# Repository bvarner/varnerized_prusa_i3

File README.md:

# Varnerized Prusa i3 3D Printer Clone

This is a project to produce a 3d printer based upon the (very excellent) work of Mr. Josef Prusa, and the 3d printing community at large.

After playing with an i3 MK2.5 my office at the time acquired I found some guides online for building your own printer inspired by the Prusa design.
Specifically, [Tom's Dolly Build](https://toms3d.org/2017/02/23/building-cheapest-possible-prusa-i3-mk2/) was highly inspiring.

I'm willing to sacrifice _some_ asthetics, a bit of performance, the 'ease' of pre-integration, and get an education for the sake of cost cutting.
As in the early heady days of the PC industry... building a 'clone' from imported components is cheaper than purchasing the fully assembled and configured machine.

## Goal of the project.

To clone a Prusa i3 with very similar mechanics, using import parts and cheaper, more-modular electronics.
My initial budget for the build is $225. With that budget, I produced a wooden framed i3 clone, using an Arduino & RAMPS board with A4988 stepper drivers, knockoff E3D V6 hotend, and an aluminum heated bed.

I have since upgraded some things considerably, in a price-conscious manner, and well behind the bleeding edge, so that I can source parts inexpensively.

This isn't just an attempt to build a clone and leave it alone. In keeping with the RepRap / Prusa mentality, my desire is to build a device that allows for replicating / designing / implementing more advanced subsequent generations.

## This Repository / Branch Strategy

The 'master' branch here will reflect the current (stable, functioning) state of the project - the machine I'm currently running, or the last state of the machine.
The 'development' branch will track be the next iteration of updates / upgrades.

# 1.3 - Volcano Hotend & Belt Tensioning
Over the years I've had problems with bearings coming loose from the x-axis ends. I held them in place with zip-ties for more than a year.
My pancake stepper with the skelestruder gave me phenomical prints, but I had many problems with stability of the hotend holding temp during high extrusion rates or aggressive part cooling fan use.

In order to print things faster (I'm sick of waiting four hours for a tiny part) and with thicker layers, I have upgraded to a Volcano knock-off hotend -- which the skelestruder supports beautifully.
I've also decided to print my entire hotend assembly in polycarbonate, as I was having multiple parts sag over time and when printing high-temp filaments (like PC or nylon).

I ended up having to upgrade to a slightly larger pancake motor, as I exceeded the torque of the tiny pancake before I exceeded the reasonable flow rate of a 0.6mm CHT volcano nozzle.

A 200g spool of PC is more than enough to print the entire extruder and omega several times over.

Credits to the folks who made these fantastic parts that I'm using:
[X-Axis](https://www.printables.com/model/394668-mk225s-x-axis-revision-with-belt-tensioner)
[Y-Axis Tensioner](https://www.printables.com/model/306303-y-axis-belt-tensioner-v2)

# 1.2 - Skelestruder.
Having some shore 95A flex filament to print, the MK3 extruder design is rubbish. I've had issues with part cooling, part visibility during print, z-axis adjustment, it's been a problem. Futhermore I get a lot of obvious print quality issues with linear advance and the direct drive extruder with 1/16th step division.
The [Skelestruder](https://www.thingiverse.com/thing:2845416) is designed to address all of that, and after having it for a few weeks, it was obvious it's a superior design.

Additionally, a friend of mine supplied me with a Prusa Mini+ filament sensor kit, which I've integrated into my build using 
this [skelestruder sensor cover](https://www.thingiverse.com/thing:4235461).

Initially I printed everything in PETG, without a silicone sock and insulation at the top of the heat block. This caused EcageS to melt a couple times, and deformed some other parts when I attempted to print Nylon at high-temperatures.
To combat this problem, I've reprinted some parts in Polycarbonate. I purchased a 200g trial spool for a reasonable fee.

* Printed Parts
    * Polycarbonate
        * SP_EcageS_r1.stl
        * SP_Omega_r2.stl
        * SP_Pinion16_r1.stl
        * SP_Pinion14_r1.stl
        * [SP_Xclamp_mk2.stl](https://www.thingiverse.com/thing:3699231)
    * PETG
        * SP_Carriage_r1.stl
        * SP_tail_b2.stl
        * SP_EcageB_r1.stl
        * SP_EcageF17_r1.stl
        * SP_Shroud_r1.stl
        * SP_Key_r1.stl
        * Inlet_ptfe_r1b.stl
        * SP_Spider17_r1.stl
        * SP_Wheel_r1.stl
        * SP_Tread56_r1.stl
        * SP_Prack_r1.stl
        * SP_Idler_r1.stl
        * SP_tensioner_b1.stl
        * SP_knob_b2.stl
        * SP_spacer_v1a4.stl
        * IR_Sensorcover_top.stl
        * IR_Sensorcover_outlet.stl
        * IR_Sensorcover_bottom.stl
        * IR_Sensor_Arm.stl
* Purchased Parts
    * [GT2 140-2GT-6](https://www.amazon.com/gp/product/B014QJBVOY/ref=ppx_yo_dt_b_asin_title_o00_s00?ie=UTF8&psc=1)
    * [Polyimide (Kapton) tape](https://www.amazon.com/gp/product/B00W3FAFP0/ref=ppx_yo_dt_b_asin_title_o04_s00?ie=UTF8&psc=1)
    * [105zz bearings](https://www.amazon.com/gp/product/B00ZHSTKCE/ref=ppx_yo_dt_b_asin_title_o07_s00?ie=UTF8&psc=1)
    * [5mmx100mm shafts](https://www.amazon.com/gp/product/B01B27MJC6/ref=ppx_yo_dt_b_asin_title_o07_s01?ie=UTF8&psc=1) I cut and shaped these with an angle grinder.
    * [12v 5015 fans](https://www.amazon.com/gp/product/B07LF1V1P1/ref=ppx_yo_dt_b_asin_title_o07_s01?ie=UTF8&psc=1) My original cooling fan died.
    * [Prusa IR filament sensor](https://www.aliexpress.com/item/32976810546.html?spm=a2g0o.productlist.0.0.115d21ee6SdBZw&algo_pvid=dfe3353a-f8a1-4ab3-83c8-9e795aa067fe&algo_exp_id=dfe3353a-f8a1-4ab3-83c8-9e795aa067fe-0)
    * [Heatblock Top Insulation](https://www.amazon.com/gp/product/B075CST527/ref=ppx_yo_dt_b_asin_title_o08_s00?ie=UTF8&psc=1) I used this between the heatbreak and the heatblock.
    * [Heatblock Silicone Sock](https://www.amazon.com/gp/product/B07Q3KHL6R/ref=ppx_yo_dt_b_asin_title_o09_s00?ie=UTF8&psc=1) How did I go so many years without a silicone sock?

# 1.1.1 - Lack Table Enclosure.
Following the [prusaprinters blog post](https://blog.prusaprinters.org/cheap-simple-3d-printer-enclosure/) on building an inexpensive (hah!) enclosure for your printer I recently picked up a couple of Ikea LACK tables.
After getting local quotes for producing the 440x440 and 440x220 acrylic panels, I opted to buy a set from a vendor on Amazon who could beat the locally sourced prices.

* Printed Parts
    * PSU Shroud
        * Compatible with the Prusa Lack table mounting clip (mounting foot geometry is closer to the Prusa part)
        * Added Lack Table PSU retainer. Similar Style as the Prusa version.
        * Text rotates to the upside down orientation on the PSU Shroud if you're rendering the LACK table parts.
    * [Ikea LACK Enclosure Main Parts](https://www.thingiverse.com/thing:2864118)
    * [Frame brace replacing the PSU for the MK3](https://www.thingiverse.com/thing:2859884)
    * [60 degree heatbed cable cover for the MK3](https://www.thingiverse.com/thing:2890592)
    * [608 bearing wheels for the adjustable spool holder](https://www.thingiverse.com/thing:3791583)
    * [Prusa Enclosure Bottom Corner with more cable space](https://www.thingiverse.com/thing:3067172)
    * [IKEA Lack Table Stack Coupler](http://www.thingiverse.com/thing:3488697)
* Purchased Parts
    * #12 AWG Silicone wire. So much better to work with than THHN.
    * XT60H Connectors
    * misc. dupont connectors & hookup wire (from the scrap bin)
    * (3) IRLB3034 N-Channel Mosfets & 10k Ohm 0805 SMT Resistors.
    * 12v RGB LED 5050 Strip (I had leftovers from another home project)
* @Home Fabricated PCB For Controlling RGB LEDs
    * Check the LEDControl directory for full KiCAD project.
    * Perfect for home-based acid etching and SMT hand soldering.
    * I use the 'laser-printer hot-iron transfer' method, and it works quite well.

# 1.1.0 - More MK3 less, MK2.
Total upgrade cost was ~$75 in January 2018.

* Heat-Bed
    * I replaced my aluminum MK3 heat bed with a magnetic MK52, 12V heat bed.
    * It's not as 'flat' as the prusa originals.
    * Cost was ~$36, as opposed to the original one which was ~$8.
    * Spring steel sheet + PEI cost around another $25. At this time, I'd opt for the powder-coated textured spring steel instead.
* Extruder
    * Uses the BondTech style extruder pulleys
    * Improved part cooling
    * 5v Noctua Fan reduces ambient noise considerably
    * I did not add a filament sensor (yet) or a dust-buffer (yet).
* Electronics
    * After having beefed up the ampacity of the RAMPS 1.4a board, and replacing the heatbed mosfet, I decided to try a RAMPS 1.6 board.
    * Much better experience than the RAMPS 1.4a.
    * After 11 months of use, no over-heating issues. No fried mosfets, no fire risk. Much better electronics from that stand point.
    * Heat bed does heat slowly, a consequence of the mosfet choice on this board, from what I understand.
    * I've updated my firmware to Marlin 1.1.9, and "Varnerized" it to match the Prusa Home Screen Asthetic on the LCD.
    * Updated RAMBo cover a bit. I ended up reprinting in PETG and got much better results than with the original PLA. It also hasn't sagged and melted in my hot-box.
* Mechanics
    * Y-Axis bearing holders have been redone, and are now my own design that allows for slight play.
    * I think I've fixed the issues with the y-axis belt holder not contacting the limit switch properly.
    * Updates to the TR8_couplings have resulted in much better Z-axis stability.
    * heatbed cable cover -- based on using ring terminals and heavy gauge speaker wire -- is _very_ large compared to the MK3.

# 1.0.0 - Hybrid MK2s & MK3
The original starting point. 1 Spool of ABS, a few scraps of cabinet grade plywood, access to a working MK2, and about $165 in imported parts.

* Heat-Bed - I chose a 3mm thick aluminum MK3 (Ultimaker clone) 200x200mm.
    * This gives me a slightly smaller build area than an Original Prusa.
    * No 'fully-automatic' skew compensation.
        * The aluminum bed of the MK3 will still work for automatic z-layer leveling.
        * Guided x-y skew measurement and compensation will be required.
    * I did pony up for a sheet of PEI plastic to cover the aluminum bed and improve adhesion. That was worth it.
* Steppers - I used an inexpensive 5-pack of 5mm output shaft steppers that put out ~40n-cm of torque.
    * My Z-Axis motors require couplings to the lead screws.
    * I did pony up for T8 ACME lead screws and nuts for the Z-axis. The small cost should be worth the improved ridgidity and accuracy.
* Electronics - Arduino Mega 2650 + RAMPS 1.4a
    * Won't be nearly as nicely packaged as a mini-rambo... until I print my own case design to make it not ugly.
    * Will have to custom-compile firmware from the Marlin project.
    * More flexibility in the long-run with regards to expansion and addition of other sensors.
    * I used a 30Amp, 12v power supply (360 Watt). I was able to get this for $20 from Amazon, which was only slightly more expensive than the best priced 240Watt imported supply. Low quantities of heavy items are expensive to ship.
    * I'm going to just bypass the poly-fuses on the RAMPS board and add properly sized inline fuses. Perhaps someday I'll replace the RAMPs board. Perhaps Not.
* Frame - I'm making mine out of wood.
    * Won't be as svelt as a Prusa from the side, and may warp / twist slightly with seasonal changes. I'll be using thing-laminations of quarter-sawn lumber or cabinet-grade plywood to minimize this.
    * Major reduction of cost here. An MK2 aluminum frame runs ~$70. Laser-cut acrylic and wood are cheaper, but less rigid, and won't be as nice as mine.
    * Basing off the MK3 frame (which uses 3030 extrusions rather than threaded rods) translates more easily to wood.
    * I have a pretty well equipped wood shop, with 40 year old tools that are accurate +- 0.254mm and within a half-degree of cross-cut. I have calipers. I'll be able to correct for skew. :-)

## Printed Parts Lineage / Changes

* Y-Axis (under heatbed carriage) -- Mostly from the MK3. The necessity of an endstop swtich necessitates some changes to the Y-Motor mount. I am expecting to need to modify the rear frame DXF to reflect modifications / changes. I may not have room for the limit switch microswitch. Also, the belt holder for y-frame may need modification.
* X-Axis (gantry above heatbed) -- Completely from the MK2s.
* Z-Axis -- Mostly from the MK3. The T8 leadscrew will likely extend beyond the upper limit of the MK3 frames upper z-ends. I modified the MK3 parts to 'open' the top of the leadscrew holes and the rod holding hole -- ala a MK2/s. I figure this will be easier than cutting a T8 rod.
* Extruder -- Completely from the MK2s. I may look into the cogged dual-feed of the MK3 at some point, but until the Prusa fillament sensor board clones start to appear, there's really no reason to do that.
    * I will need to wait until my induction probe arrives to make sure it's the same physical size as the PINDA and avoid re-printing.
    * Thankfully for the Z-axis I don't need an end-stop limit switch.
* LCD -- Assuming my LCD fits the frame properly, I'll use the Prusa design...

### Print Settings

Prusa uses ABS, 20% infill, 3 perimeter (vertical) shells on a 0.4mm nozzle. The rest, well that's up to you. :-)
The three vertical shells are incredibly important. The extra ridigity / support is _really_ necessary, or you're likely to break idler parts.

### BOM

The basic BOM is:

| Part | Quantity |
| ---- | --------:| 
| [extruder-body.stl](Printed-Parts/stl/extruder-body.stl) | 1 |
| [extruder-cover.stl](Printed-Parts/stl/extruder-cover.stl) | 1 |
| [extruder-idler.stl](Printed-Parts/stl/extruder-idler.stl) | 1 |
| [fan_nozzle.stl](Printed-Parts/stl/fan_nozzle.stl) | 1 |
| [LCD-cover-Varnerized-MK3.stl](Printed-Parts/stl/LCD-cover-Varnerized-MK3.stl) | 1 |
| [lcd-supports.stl](Printed-Parts/stl/lcd-supports.stl) | 1 |
| [lcd-knob.stl](Printed-Parts/stl/lcd-knob.stl) | 1 |
| [x-carriage.stl](Printed-Parts/stl/x-carriage.stl) | 1 |
| [x-end-idler.stl](Printed-Parts/stl/x-end-idler.stl) | 1 |
| [x-end-motor.stl](Printed-Parts/stl/x-end-motor.stl) | 1 |
| [y-belt-holder.stl](Printed-Parts/stl/y-belt-holder.stl) | 1 |
| [y-belt-idler.stl](Printed-Parts/stl/y-belt-idler.stl) | 1 |
| [y-holder.stl](Printed-Parts/stl/y-holder.stl) | 4 |
| [y-motor-holder.stl](Printed-Parts/stl/y-motor-holder.stl) | 1 |
| [z-axis-bottom.stl](Printed-Parts/stl/z-axis-bottom.stl) | 1 |
| [z-axis-top.stl](Printed-Parts/stl/z-axis-top.stl) | 1 |

Optionally, I highly recommend you print the spool holder, RAMPS (Rambo) case, psu shroud, etc. or: model your own.

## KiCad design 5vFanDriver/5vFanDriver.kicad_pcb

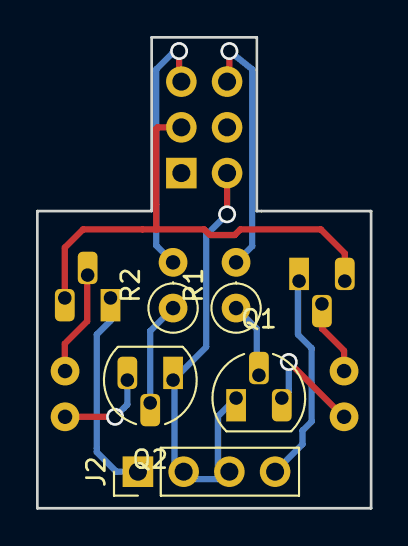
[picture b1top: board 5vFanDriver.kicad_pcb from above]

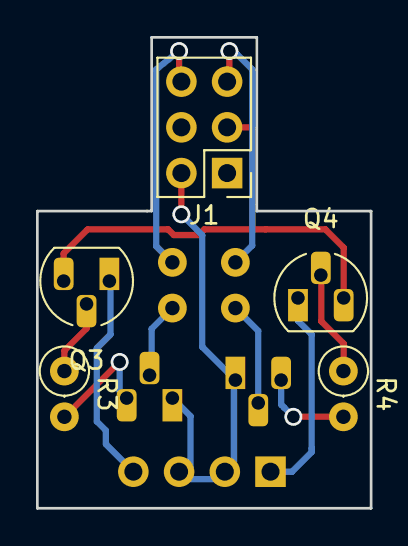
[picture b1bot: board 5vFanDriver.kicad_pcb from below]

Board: 2 copper layers, 18.5 x 26.2 mm, 10 parts (5 on the bottom side), 12 nets.

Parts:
J1: Conn_02x03_Odd_Even; PinHeader_2x03_P2.54mm_Vertical
J2: Conn_01x04_Male; PinHeader_1x04_P2.54mm_Vertical
Q1, Q2: 2N3904; TO-92_HandSolder
Q3, Q4: 2N3906; TO-92_HandSolder
R1, R2: 1k; R_Axial_DIN0207_L6.3mm_D2.5mm_P2.54mm_Vertical
R3, R4: 100; R_Axial_DIN0207_L6.3mm_D2.5mm_P2.54mm_Vertical

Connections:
unnamed: J1.2, J2.2, J2.3, Q1.1, Q2.1
unnamed: J1.3, Q3.3, Q4.3
unnamed: J1.5, R2.2
unnamed: J1.6, R1.2
unnamed: J2.1, Q4.1
unnamed: J2.4, Q3.1
unnamed: Q1.2, R1.1
unnamed: Q1.3, R3.2
unnamed: Q2.2, R2.1
unnamed: Q2.3, R4.2
unnamed: Q3.2, R3.1
unnamed: Q4.2, R4.1

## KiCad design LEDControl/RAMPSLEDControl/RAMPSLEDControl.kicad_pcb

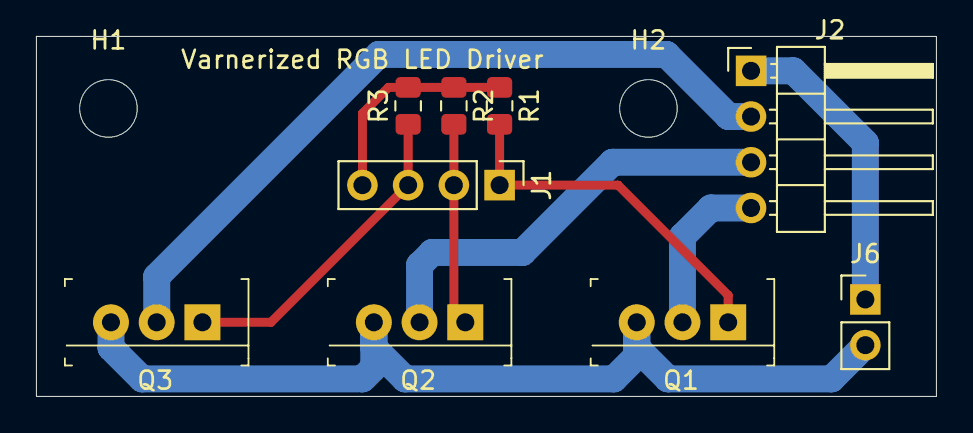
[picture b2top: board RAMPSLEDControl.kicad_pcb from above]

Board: 2 copper layers, 50.0 x 20.0 mm, 11 parts (0 on the bottom side), 9 nets.

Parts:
H1, H2: MountingHole; MountingHole_3.2mm_M3_DIN965
J1: Conn_01x04_Male; PinHeader_1x04_P2.54mm_Vertical
J2: Conn_01x04_Male; PinHeader_1x04_P2.54mm_Horizontal
J6: Conn_01x02_Male; PinHeader_1x02_P2.54mm_Vertical
Q1, Q2, Q3: IRLB3034PBF; TO-220-3
R1, R2, R3: 10K; R_0805_2012Metric_Pad1.15x1.40mm_HandSolder

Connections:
unnamed: J1.1, Q1.1, R1.2
unnamed: J1.2, Q2.1, R2.2
unnamed: J1.3, Q3.1, R3.1
unnamed: J1.4, R1.1, R2.1, R3.2
unnamed: J2.1, J6.1
unnamed: J2.2, Q3.2
unnamed: J2.3, Q2.2
unnamed: J2.4, Q1.2
unnamed: J6.2, Q1.3, Q2.3, Q3.3

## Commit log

2018-01-05 Here we go. initial commit of my effort to turn the MK3 dxfs into STLs that can be used as a template.
2018-01-06 Adding the readme.
2018-01-06 README.md
2018-01-09 Updates to the frame
2018-01-10 Major adjustment. This should actually work now.
2018-01-10 All sectors
2018-01-10 Named folder to match original Prusa
2018-01-11 Updates...
2018-01-11 Updates on some things
2018-01-11 Added the files and updates
2018-01-11 Table of things to print.
2018-01-11 Test of link
2018-01-11 Links.
2018-01-11 Hey, this really is 0.1.0...
2018-01-11 Here we go. Print settings.
2018-01-11 subheading
2018-01-17 Bumped all this to 6mm thick, which is ~2x as thick
2018-01-18 Updated the Extruder Body to move the P.I.N.D.A and Fan cable tray 'up' the extruder body, making more room for the non-Prusa 5mm probes, which seem to be longer.
2018-01-18 Better font on the Varnerized bits.
2018-01-20 * Customized for smaller microswitch on the x-end. * Customized for T8 lead screws and accompanying brass z-nut rather than the Original Prusa bits.
2018-01-20 Modifying endstop location and hole spacing to match my microswitches.
2018-01-21 Adding the motor couplings for the z-axis.
2018-01-21 rotate for printing
2018-01-24 Added a PSU shroud. Wow. I really hate this scad source. It's nasty.
2018-01-26 A 'clean room' remix of the PSU cover, based upon measurements from my PSU.
2018-01-26 Added pretty corners.
2018-01-26 Adjustments to hole locations, based on a print result.
2018-01-26 Updated Y-belt holder and motor mount.
2018-01-28 Updates to the y-belt-holder for limit switch clearance.
2018-01-30 Undoing the unnecessary (and it would be kinda catastrophic) offset for the induction probe. Adding the cable holder.
2018-01-30 Some updates here...
2018-01-30 Added the POT cutout for the LCD supports. I chopped my finger with a steak knife manually making this modification....
2018-02-17 Many adjustments based on working with the printer for a few days.
    * RAMBo based RAMPS cover. Lifted the original work from thingiverse. Proper credit in the files.
    * Reverse-engineered the lcd_knob with my micrometer and produced some openscad source. I have a reprint in progress (at 0.05 layers) I may have to tune this again.
    * The TR8 couplings have been updated with a longer D-shaft end, and a 'skirt' added to keep things from falling into the bearings.
    * Updates to the psu shroud, which I highly recommend you _don't_ print in ABS... unless you like layers stressing and breaking. I'll try it in PLA next time, but may end up springing for some nylon 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
2018-02-18 * LCD Knob. Because the Prusa repo used an STL to import into the SCAD (what the heck?) So I "clean-roomed" it from a physical print and my caliper. * A bit more pronounced recess in the PSU Shroud.
2018-02-19 Minor tweaks to existing parts, and a spool holder.
    * PSU Shroud: Embossed the text a bit more.
    * TR8_coupling: Added a skirt to keep bits of plastic out of the bearing area. (probably totally unnecessary)
    * Added a Spool holder, inspired heavily by Martin Majewski's https://www.thingiverse.com/thing:1832235, but built with OpenSCAD.
    * I was just going to use Martin's, but I couldn't customize it properly to expand the hook area to accomodate the thickness of my frame. Bummer.
    * Only three printable parts. Arm, threaded bearing holder, nut..
    * Uses 608 bearings, without a need for a 'tire'.
2018-02-27 Resync of the Rambo cover from thingiverse with the one from Prusa.
    Did some modifications to make an 80mm fan fit, but unfortunately, it's rubbing some things in there, so I haven't been able to mount it. :-/
2018-02-27 Apparently I forgot to -a on the last commit.
2018-02-27 Updated the X-Ends to have a proper nut-trap for the brass TR-8 nuts.
2018-02-27 Minor README Updates.
2018-05-31 Minor update to readme.
2019-04-23 feat: A 5v PWM Fan Driver for the RAMPS board. fix: New bearing holder for the Y-Axis. feat: New, better z-axis couplers. feat: Fixed the y carriage belt holder. Forgot I had to actually cut part of 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
2019-04-23 Updating some of these.
2019-10-05 Updated quite a few things. I've lost count. I think this is the RAMBo cover.
2019-10-05 I should clean these up later. Some of these cases are probably not the right one.
2020-01-06 * Added a retainer (loosely based upon the Prusa one) for the PSU when mounting upside down on an Ikea LACK table. * Added a parameter for lack_table mounts which adds the upper retainer and flips th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
2020-01-06 * Rendered PSU shroud that more closely matches the Prusa geometry (for the support foot) * Updated for LACK table mounting.
2020-01-06 Removing this disaster. :-)
2020-01-06 Updating for the MK3 work done in early 2018.
2020-01-06 Lack table updates
2020-01-07 bearing wheels are the best wheels.
2020-02-04 Adding a KiCad Project that functions as an LED light control for 12v RGB lights.
2020-02-04 Parameterized the cable clearance.
2020-02-04 Updates to the LACK table spacing.
2020-02-05 Nozzle fan holder STLs and the MK3 extruder body.
2020-02-05 * MK3 nozzle-fan. Somehow I missed having this exported to STL. * LEDControl project and PCB bits. * Updated Readme.
2020-03-20 * Some minor cleanup and adjustments to the z-axis couplings. * Additional SCAD syntax cleanup. * Added the PrusaSlicer config.
2021-08-31 Updating a few parts from a recent revision.
2021-08-31 Minor Revisions to the stock prusa bits.
2021-08-31 Skelestruder V1! * Cleanup older prusa parts that we don't use. * Add new skelestruder parts.
2021-09-06 Adding documentation for using the Skelestruder. I really like it's functionality. I'm hoping the Polycarbonate parts will avoid the 'melting' issues I've had with high-temperature filaments.
2024-03-28 feat: Update X-Axis ends. feat: Update Y-Axis tensioner. feat: Updated to Skelestruder Volcano, and printed more parts in PC.
2025-07-23 chore: Pushing updates from my local machine. I'm not sure what changed here, it's been a _long_ time.
